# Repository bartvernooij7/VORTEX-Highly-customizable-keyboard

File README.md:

# VORTEX-Highly-customizable-keyboard
this a split keyboard that i made with a friend. it is highly customizable so you can change it to your'e linking

i have made this project with pixelrift and my self 
he has made 3dmodel for the keyboard
my task was to make the pcb, there whil be two versions: one is without a exstra screen and rotary encoder and the other version does have a rotaryencoder and 1.5 inch screen on the right half that can be used for volume control and dispalying lost of diffrent things like: pc status, mesages or spotify

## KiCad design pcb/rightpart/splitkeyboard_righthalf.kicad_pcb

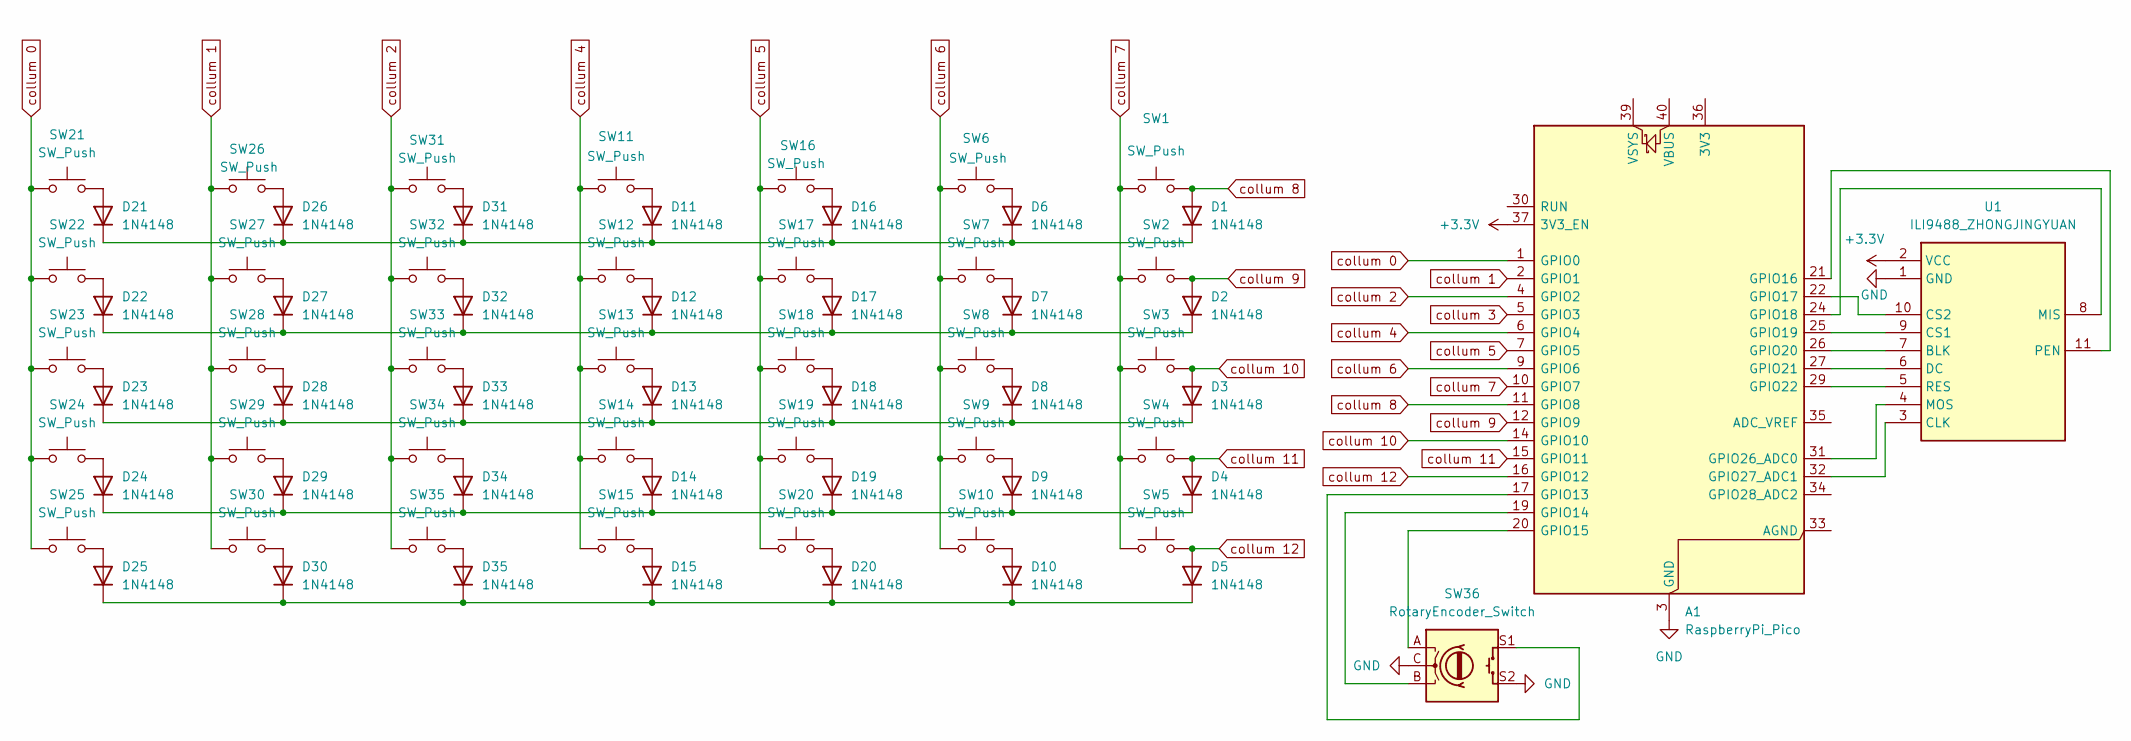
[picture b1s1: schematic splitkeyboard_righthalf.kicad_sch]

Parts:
A1: RaspberryPi_Pico; RaspberryPi_Pico_Common_Unspecified
D1, D2, D3, D4, D5, D6, D7, D8, D9, D10, D11, D12, D13, D14, D15, D16, D17, D18, D19, D20, D21, D22, D23, D24, D25, D26, D27, D28, D29, D30, D31, D32, D33, D34, D35: 1N4148; D_DO-35_SOD27_P7.62mm_Horizontal
SW1, SW2, SW3, SW4, SW5, SW6, SW7, SW8, SW9, SW10, SW11, SW12, SW13, SW14, SW15, SW16, SW17, SW18, SW19, SW20, SW21, SW22, SW23, SW24, SW25, SW26, SW27, SW28, SW29, SW30, SW31, SW32, SW33, SW34, SW35: SW_Push; MX100H
SW36: RotaryEncoder_Switch; RotaryEncoder_Alps_EC11E-Switch_Vertical_H20mm
U1: ILI9488_ZHONGJINGYUAN; ILI9488_11Pin

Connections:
+3.3V: A1.37 (3V3_EN), U1.2 (VCC)
GND: A1.3 (GND), A1.8 (GND), A1.13 (GND), A1.18 (GND), A1.23 (GND), A1.28 (GND), A1.38 (GND), SW36.C, SW36.S2, U1.1 (GND)
unnamed: A1.17 (GPIO13), SW36.S1
unnamed: A1.19 (GPIO14), SW36.B
unnamed: A1.20 (GPIO15), SW36.A
unnamed: A1.21 (GPIO16), U1.11 (PEN)
unnamed: A1.22 (GPIO17), U1.10 (CS2)
unnamed: A1.24 (GPIO18), U1.8 (MIS)
unnamed: A1.25 (GPIO19), U1.9 (CS1)
unnamed: A1.26 (GPIO20), U1.7 (BLK)
unnamed: A1.27 (GPIO21), U1.6 (DC)
unnamed: A1.29 (GPIO22), U1.5 (RES)
unnamed: A1.31 (GPIO26_ADC0), U1.4 (MOS)
unnamed: A1.32 (GPIO27_ADC1), U1.3 (CLK)
unnamed: D1.1 (K), D6.1 (K), D11.1 (K), D16.1 (K), D21.1 (K), D26.1 (K), D31.1 (K)
unnamed: D6.2 (A), SW6.2
unnamed: D7.2 (A), SW7.2
unnamed: D8.2 (A), SW8.2
unnamed: D9.2 (A), SW9.2
unnamed: D10.2 (A), SW10.2
unnamed: D5.1 (K), D10.1 (K), D15.1 (K), D20.1 (K), D25.1 (K), D30.1 (K), D35.1 (K)
unnamed: D11.2 (A), SW11.2
unnamed: D12.2 (A), SW12.2
unnamed: D2.1 (K), D7.1 (K), D12.1 (K), D17.1 (K), D22.1 (K), D27.1 (K), D32.1 (K)
unnamed: D13.2 (A), SW13.2
unnamed: D3.1 (K), D8.1 (K), D13.1 (K), D18.1 (K), D23.1 (K), D28.1 (K), D33.1 (K)
unnamed: D14.2 (A), SW14.2
unnamed: D4.1 (K), D9.1 (K), D14.1 (K), D19.1 (K), D24.1 (K), D29.1 (K), D34.1 (K)
unnamed: D15.2 (A), SW15.2
unnamed: D16.2 (A), SW16.2
unnamed: D17.2 (A), SW17.2
unnamed: D18.2 (A), SW18.2
unnamed: D19.2 (A), SW19.2
unnamed: D20.2 (A), SW20.2
unnamed: D21.2 (A), SW21.2
unnamed: D22.2 (A), SW22.2
unnamed: D23.2 (A), SW23.2
unnamed: D24.2 (A), SW24.2
unnamed: D25.2 (A), SW25.2
unnamed: D26.2 (A), SW26.2
unnamed: D27.2 (A), SW27.2
unnamed: D28.2 (A), SW28.2
unnamed: D29.2 (A), SW29.2
unnamed: D30.2 (A), SW30.2
unnamed: D31.2 (A), SW31.2
unnamed: D32.2 (A), SW32.2
unnamed: D33.2 (A), SW33.2
unnamed: D34.2 (A), SW34.2
unnamed: D35.2 (A), SW35.2
collum 0: A1.1 (GPIO0), SW21.1, SW22.1, SW23.1, SW24.1, SW25.1
collum 1: A1.2 (GPIO1), SW26.1, SW27.1, SW28.1, SW29.1, SW30.1
collum 2: A1.4 (GPIO2), SW31.1, SW32.1, SW33.1, SW34.1, SW35.1
collum 3: A1.5 (GPIO3)
collum 4: A1.6 (GPIO4), SW11.1, SW12.1, SW13.1, SW14.1, SW15.1
collum 5: A1.7 (GPIO5), SW16.1, SW17.1, SW18.1, SW19.1, SW20.1
collum 6: A1.9 (GPIO6), SW6.1, SW7.1, SW8.1, SW9.1, SW10.1
collum 7: A1.10 (GPIO7), SW1.1, SW2.1, SW3.1, SW4.1, SW5.1
collum 8: A1.11 (GPIO8), D1.2 (A), SW1.2
collum 9: A1.12 (GPIO9), D2.2 (A), SW2.2
collum 10: A1.14 (GPIO10), D3.2 (A), SW3.2
collum 11: A1.15 (GPIO11), D4.2 (A), SW4.2
collum 12: A1.16 (GPIO12), D5.2 (A), SW5.2

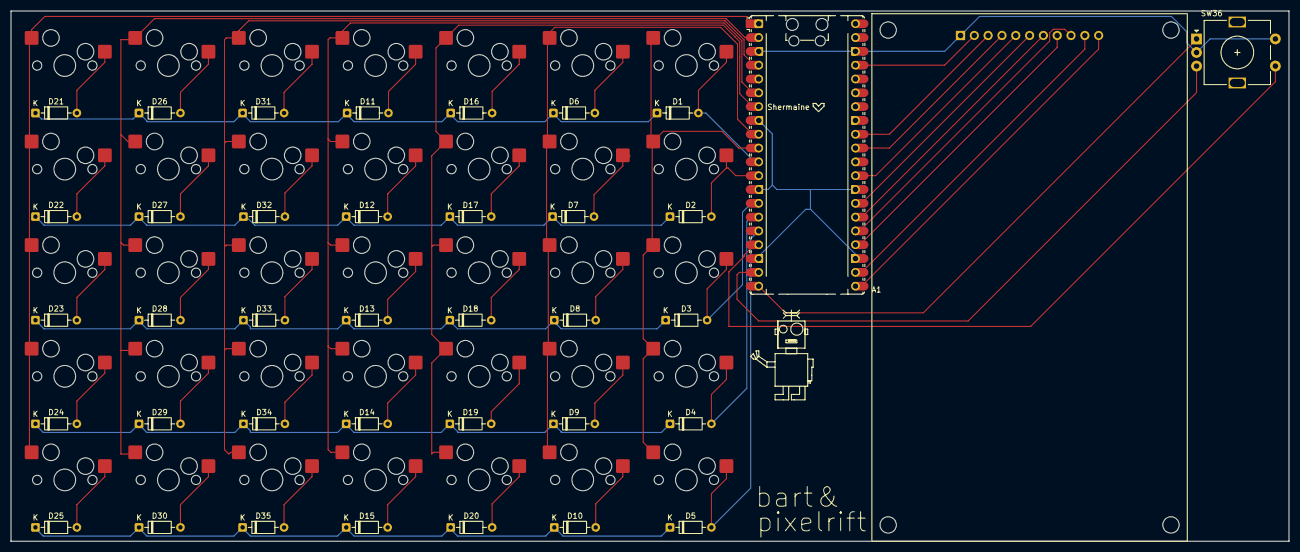
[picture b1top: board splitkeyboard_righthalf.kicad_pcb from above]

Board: 2 copper layers, 235.0 x 97.5 mm, 73 parts (0 on the bottom side), 61 nets.
